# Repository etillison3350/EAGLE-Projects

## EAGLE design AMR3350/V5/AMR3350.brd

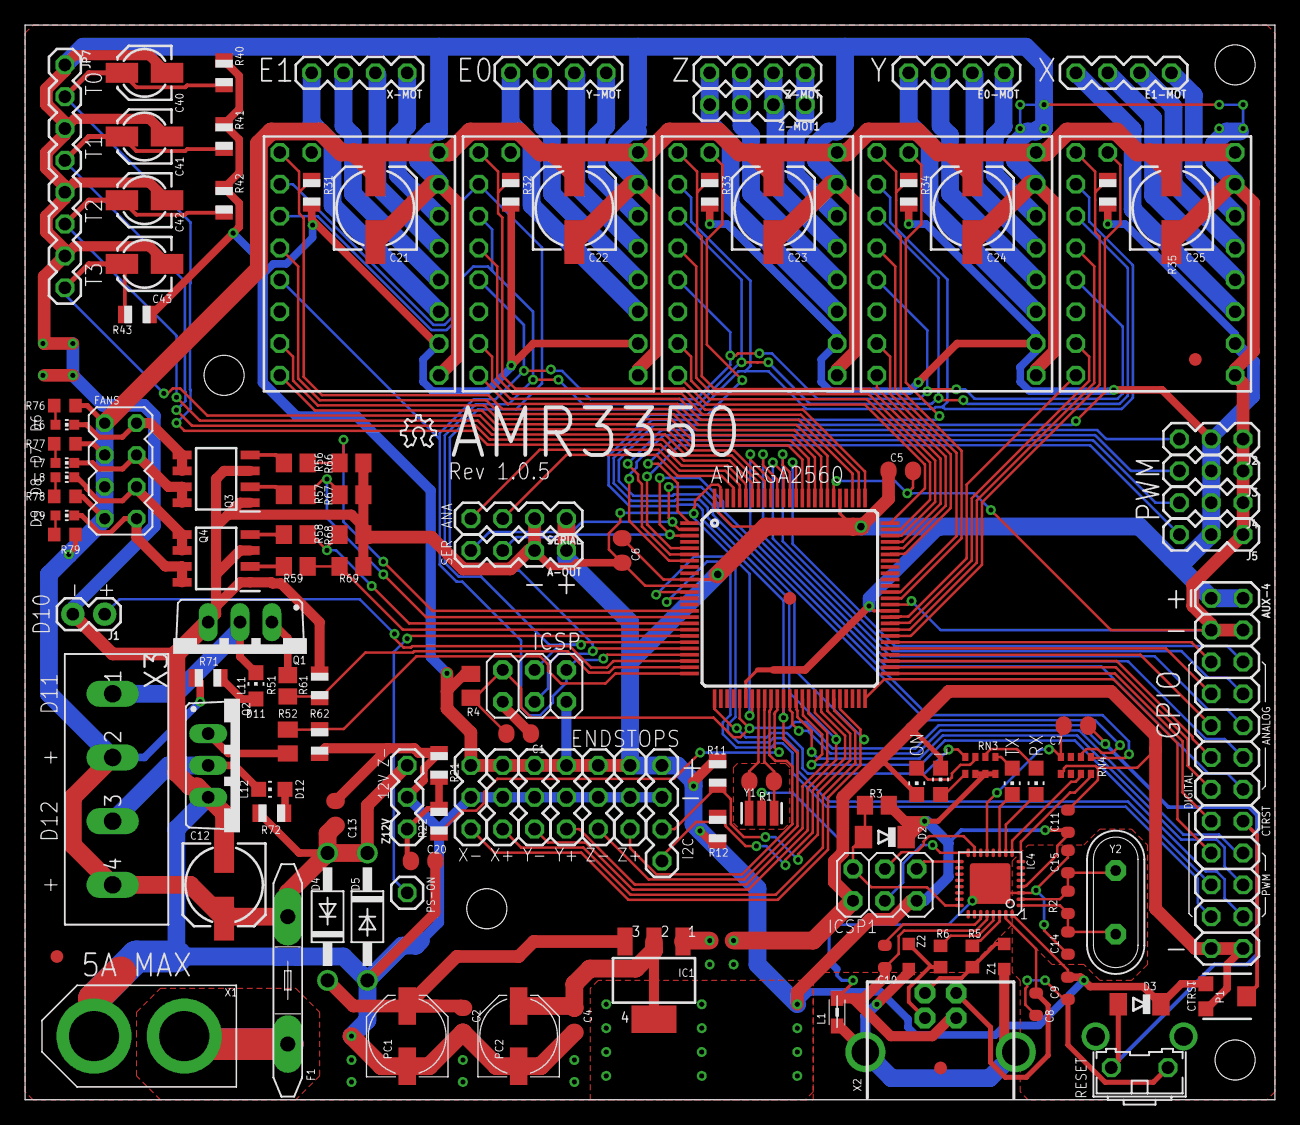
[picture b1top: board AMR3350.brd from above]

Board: 2 copper layers, 99.7 x 85.7 mm, 135 parts (1 on the bottom side), 141 nets.

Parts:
A-OUT: 1X04_SMALL
ATMEGA2560: ATMEGA2560-16AU; TQFP100
AUX-4: CONN_12X2SMALL; 2X12_SMALL
C1: 22p; C0805RND
C2, C4, C5, C6, C7, C13, C20: 100n; C0805RND
C8, C9, C11: 100n; C0603-ROUND
C10: 1u; C0603-ROUND
C12, C21, C22, C23, C24, C25: 100uF; 153CLV-0605
C14, C15: 22p; C0603-ROUND
C40, C41, C42, C43: 10uF; 153CLV-0405
D2, D3: CD1206-S01575; MINIMELF
D4, D5: 1N4004; DO41-10
E0-MOT, E1-MOT: 1X04_SMALL
F1: MFR500
FANS: M04X2; 2X4
FD1, FD2, FD3, FD4: FIDUCIALMOUNT; FIDUCIA-MOUNT
GND: 0; R0201
I2C: 1X04_SMALL
IC1: NCP1117ST50T3G; SOT223
IC4: ATMEGA16U2-MU; MLF32
ICSP, ICSP1: 3x2M; 2X03
J1: 1X02
J2, J3, J4, J5: 455-1750-1-ND; 1X03_SMALL
JP7: 1X08_SMALL
L: RED; CHIP-LED0805
L1: BLM21; 0805
L6, L7, L8, L9: CHIP-LED0603
L11, L12: CHIP-LED0805
LOGO2: OSHW_LOGO_6MILX0100-NT; OSHW_6X100_NOTEXT
ON: GREEN; CHIP-LED0805
P1: TC33X-2-103E; TC33X-2_1
PC1, PC2: 47u; PANASONIC_D
PS-ON: 1X01_SMALL
Q1, Q2: STP55NF06L; TO220BV
Q3, Q4: SI4946CDY-T1-GE3; SOIC127P600X175-8N
R1: 1M; R0805RND
R2: 1M; R0603-ROUND
R3, R4, R21, R31, R32, R33, R34, R35: 10k; R0805
R5, R6: 22R; R0603
R11, R12: 3.3K; R0805
R22: 15k; R0805
R40, R41, R42, R43: 4.7K; R0805
R51: 10r; R0805
R52: 10r; M0805
R56, R57, R58, R59: 10R; R0805
R61, R62, R66, R67, R68, R69: 100k; R0805
R71, R72: 1.8K; R0805
R76, R77, R78, R79: R0603
RESET: B3F-31XX
RN3, RN4: 1k; CAY16
RX: YELLOW; CHIP-LED0805
SERIAL: 1X04_SMALL
TX: YELLOW; CHIP-LED0805
U$1, U$2, U$3, U$4, U$5: TMC2130BREAKOUT
X1: XT60
X2: USB-B_TH; PN61729-NOSILK
X3: 4-PIN
X+: 455-1750-1-ND; 1X03_SMALL
X-: 455-1750-1-ND; 1X03_SMALL
X-MOT: 1X04_SMALL
Y1: CSTCE16M0V53-R0 16MHZ; RESONATOR
Y2: 16MHz; QS
Y+: 455-1750-1-ND; 1X03_SMALL
Y-: 455-1750-1-ND; 1X03_SMALL
Y-MOT: 1X04_SMALL
Z1, Z2: CG0603MLC-05E; CT/CN0603
Z12V: 455-1750-1-ND; 1X03_SMALL
Z+: 455-1750-1-ND; 1X03_SMALL
Z-: 455-1750-1-ND; 1X03_SMALL
Z-MOT, Z-MOT1: 1X04_SMALL

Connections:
12V-IN: F1.2, X1.P$1
+5V: A-OUT.1, ATMEGA2560.10, ATMEGA2560.31, ATMEGA2560.61, ATMEGA2560.80, ATMEGA2560.100, AUX-4.1, AUX-4.2, C4.1, C5.1, C6.1, C9.1, C11.1, D2.C, D3.C, I2C.1, IC1.2, IC1.4, IC4.4, IC4.32, ICSP.2, ICSP1.2, J2.2, J3.2, J4.2, J5.2, P1.1, PC2.+, R3.2, R4.2, R11.2, R12.2, R31.1, R32.1, R33.1, R34.1, R35.1, R40.2, R41.2, R42.2, R43.2, RN3.2, RN3.3, RN3.4, SERIAL.1, U$1.VIO, U$2.VIO, U$3.VIO, U$4.VIO, U$5.VIO, X+.3, X-.3, Y+.3, Y-.3, Z+.3, Z-.3
+12V: C12.+, C13.1, C21.+, C22.+, C23.+, C24.+, C25.+, D4.A, D5.C, F1.1, FANS.1, FANS.3, FANS.5, FANS.7, R71.1, R72.1, R76.2, R77.2, R78.2, R79.2, U$1.VM, U$2.VM, U$3.VM, U$4.VM, U$5.VM, X3.2, X3.4, Z12V.3
A0: ATMEGA2560.97, SERIAL.3
A1: ATMEGA2560.96, SERIAL.4
A2: ATMEGA2560.95, C40.+, JP7.2, R40.1
A3: ATMEGA2560.94, C41.+, JP7.4, R41.1
A4: ATMEGA2560.93, C42.+, JP7.6, R42.1
A5: ATMEGA2560.92, C43.+, JP7.8, R43.1
A6: ATMEGA2560.91, AUX-4.14
A7: ATMEGA2560.90, AUX-4.12
A8: ATMEGA2560.89, AUX-4.10
A9: ATMEGA2560.88, AUX-4.8
A10: ATMEGA2560.87, AUX-4.6
A11: ATMEGA2560.86, U$1.DIR
A12: ATMEGA2560.85, U$1.STEP
A13: ATMEGA2560.84, U$1.CFG-3
A14: ATMEGA2560.83, R31.2, U$1.CFG-6
A15: ATMEGA2560.82, U$2.DIR
CTRST: AUX-4.16, P1.2
D0: A-OUT.4, ATMEGA2560.2, RN4.2
D1: A-OUT.3, ATMEGA2560.3, RN4.1
D2: ATMEGA2560.6, J2.3
D3: ATMEGA2560.7, J3.3
D4: ATMEGA2560.1, J4.3
D5: ATMEGA2560.5, J5.3
D6: ATMEGA2560.15, R56.1, R66.1
D7: ATMEGA2560.16, R57.1, R67.1
D8: ATMEGA2560.17, R58.1, R68.1
D9: ATMEGA2560.18, R59.1, R69.1
D10: ATMEGA2560.23, J1.1
D11: ATMEGA2560.24, R51.1, R61.1
D12: ATMEGA2560.25, R52.1, R62.1
D13(LED): ATMEGA2560.26, RN3.8
D14: ATMEGA2560.64, U$5.CFG-3
D15: ATMEGA2560.63, R34.2, U$5.CFG-6
D16: ATMEGA2560.13, AUX-4.21
D17: ATMEGA2560.12, AUX-4.19
D18: ATMEGA2560.46, U$4.IREF, X-.1
D19: ATMEGA2560.45, X+.1
D22: ATMEGA2560.78, U$2.STEP
D23: ATMEGA2560.77, U$2.CFG-3
D24: ATMEGA2560.76, R32.2, U$2.CFG-6
D25: ATMEGA2560.75, U$3.DIR
D26: ATMEGA2560.74, U$3.STEP
D27: ATMEGA2560.73, U$3.CFG-3
D28: ATMEGA2560.72, R33.2, U$3.CFG-6
D29: ATMEGA2560.71, U$5.DIR
D30: ATMEGA2560.60, U$4.DIR
D31: ATMEGA2560.59, U$4.STEP
D32: ATMEGA2560.58, U$4.CFG-3
D33: ATMEGA2560.57, R35.2, U$4.CFG-6
D34: ATMEGA2560.56, AUX-4.5
D35: ATMEGA2560.55, AUX-4.7
D36: ATMEGA2560.54, AUX-4.9
D37: ATMEGA2560.53, AUX-4.11
D38: ATMEGA2560.50, AUX-4.17
D39: ATMEGA2560.70, U$5.STEP
D40: ATMEGA2560.52, AUX-4.13
D41: ATMEGA2560.51, AUX-4.15
D42: ATMEGA2560.42, U$5.IREF, Y-.1
D43: ATMEGA2560.41, Y+.1
D44: ATMEGA2560.40, AUX-4.22
D45: ATMEGA2560.39, AUX-4.20
D46: ATMEGA2560.38, AUX-4.18
D47: ATMEGA2560.37, U$3.IREF, Z-.1
D48: ATMEGA2560.36, R22.1
D49: ATMEGA2560.35, Z+.1
D53: ATMEGA2560.19, PS-ON.1
D+: R6.2, X2.3, Z2.2
D-: R5.2, X2.2, Z1.2
DTR: C7.1, IC4.13, RN4.4
E0-1: E0-MOT.1, U$5.OB2
E0-2: E0-MOT.2, U$5.OB1
E0-3: E0-MOT.3, U$5.OA1
E0-4: E0-MOT.4, U$5.OA2
E1-1: E1-MOT.1, U$4.OB2
E1-2: E1-MOT.2, U$4.OB1
E1-3: E1-MOT.3, U$4.OA1
E1-4: E1-MOT.4, U$4.OA2
GND: A-OUT.2, ATMEGA2560.11, ATMEGA2560.32, ATMEGA2560.62, ATMEGA2560.81, ATMEGA2560.99, AUX-4.3, AUX-4.4, AUX-4.23, AUX-4.24, C1.2, C2.2, C4.2, C5.2, C6.2, C8.2, C9.2, C11.2, C12.-, C13.2, C14.2, C15.2, C20.2, C21.-, C22.-, C23.-, C24.-, C25.-, C40.-, C41.-, C42.-, C43.-, D5.A, GND.2, I2C.2, IC1.1, IC4.3, IC4.33, ICSP.6, ICSP1.6, J1.2, J2.1, J3.1, J4.1, J5.1, JP7.1, JP7.3, JP7.5, JP7.7, L.C, ON.C, P1.3, PC1.-, PC2.-, Q1.S, Q2.S, Q3.1, Q3.3, Q4.1, Q4.3, R21.1, R61.2, R62.2, R66.2, R67.2, R68.2, R69.2, RESET.2, RN4.5, SERIAL.2, U$1.GND, U$1.GND@0, U$2.GND, U$2.GND@0, U$3.GND, U$3.GND@0, U$4.GND, U$4.GND@0, U$5.GND, U$5.GND@0, X1.P$2, X+.2, X-.2, Y1.2, Y+.2, Y-.2, Z12V.2, Z+.2, Z-.2
L: L.A, RN3.1
M8RXD: IC4.9, RN4.7
M8TXD: IC4.8, RN4.8
MISO: ATMEGA2560.22, ICSP.1, U$1.CFG-0, U$2.CFG-0, U$3.CFG-0, U$4.CFG-0, U$5.CFG-0
MISO2: IC4.17, ICSP1.1
MOSI: ATMEGA2560.21, ICSP.4, U$1.CFG-1, U$2.CFG-1, U$3.CFG-1, U$4.CFG-1, U$5.CFG-1
MOSI2: IC4.16, ICSP1.4
unnamed: L9.A, R79.1
unnamed: L8.A, R78.1
unnamed: C20.1, R21.2, R22.2, Z12V.1
unnamed: L6.A, R76.1
unnamed: L7.A, R77.1
unnamed: L12.A, R72.2
unnamed: L11.A, R71.2
ON: ON.A, RN3.7
Q1-D: L11.C, Q1.D, X3.1
Q1-G: Q1.G, R51.2
Q2-D: L12.C, Q2.D, X3.3
Q2-G: Q2.G, R52.2
Q6-D: FANS.2, L6.C, Q3.5, Q3.6
Q6-G: Q3.4, R56.2
Q7-D: FANS.4, L7.C, Q3.7, Q3.8
Q7-G: Q3.2, R57.2
Q8-D: FANS.6, L8.C, Q4.5, Q4.6
Q8-G: Q4.4, R58.2
Q9-D: FANS.8, L9.C, Q4.7, Q4.8
Q9-G: Q4.2, R59.2
RD+: IC4.29, R6.1
RD-: IC4.30, R5.1
RESET: ATMEGA2560.30, C1.1, C7.2, D3.A, ICSP.5, R4.1, RESET.1
RESET2: D2.A, IC4.24, ICSP1.5, R3.1
RX: RN3.6, RX.A
RXL: IC4.10, RX.C
SCK: ATMEGA2560.20, ICSP.3, U$1.CFG-2, U$2.CFG-2, U$3.CFG-2, U$4.CFG-2, U$5.CFG-2
SCK2: IC4.15, ICSP1.3
SCL: ATMEGA2560.43, I2C.4, R12.1
SDA: ATMEGA2560.44, I2C.3, R11.1
TX: RN3.5, TX.A
TXL: IC4.11, TX.C
UGND: C10.2, GND.1, IC4.28, L1.1, X2.4
USBVCC: C8.1, IC4.31, X2.1
USHIELD: L1.2, X2.P$1, X2.P$2, Z1.1, Z2.1
VIN: C2.1, D4.C, IC1.3, PC1.+
VUCAP: C10.1, IC4.27
X-1: U$1.OB2, X-MOT.1
X-2: U$1.OB1, X-MOT.2
X-3: U$1.OA1, X-MOT.3
X-4: U$1.OA2, X-MOT.4
XT1: C14.1, IC4.1, R2.1, Y2.2
XT2: C15.1, IC4.2, R2.2, Y2.1
XTAL1: ATMEGA2560.34, R1.1, Y1.3
XTAL2: ATMEGA2560.33, R1.2, Y1.1
Y-1: U$2.OB2, Y-MOT.1
Y-2: U$2.OB1, Y-MOT.2
Y-3: U$2.OA1, Y-MOT.3
Y-4: U$2.OA2, Y-MOT.4
Z-1: U$3.OB2, Z-MOT.1, Z-MOT1.1
Z-2: U$3.OB1, Z-MOT.2, Z-MOT1.2
Z-3: U$3.OA1, Z-MOT.3, Z-MOT1.3
Z-4: U$3.OA2, Z-MOT.4, Z-MOT1.4

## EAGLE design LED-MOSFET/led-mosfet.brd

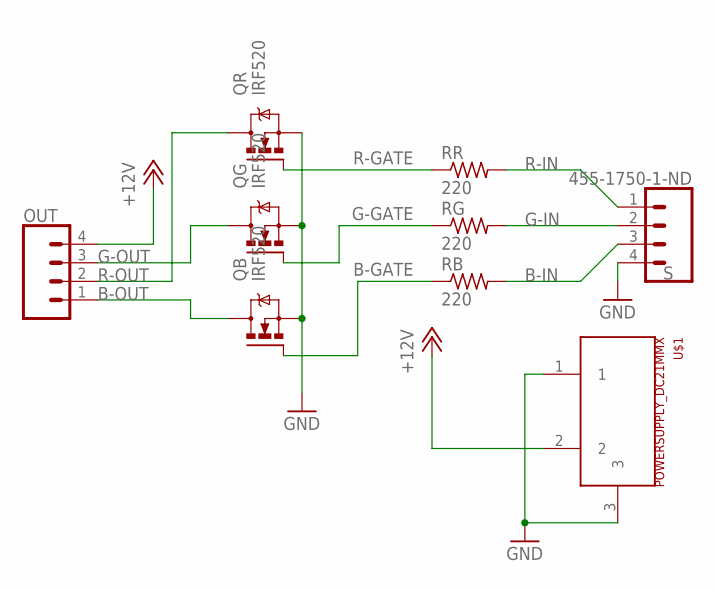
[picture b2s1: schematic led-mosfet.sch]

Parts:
OUT: CONN_04; 1X04
QB: IRF520; TO220BV
QG: IRF520; TO220BV
QR: IRF520; TO220BV
RB: 220; R0805
RG: 220; R0805
RR: 220; R0805
S: 455-1750-1-ND; 1X04
U$1: POWERSUPPLY_DC21MMX; POWERSUPPLY_DC-21MM

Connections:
+12V: OUT.4, U$1.2
B-GATE: QB.G, RB.1
B-IN: RB.2, S.3
B-OUT: OUT.1, QB.D
G-GATE: QG.G, RG.1
G-IN: RG.2, S.2
G-OUT: OUT.3, QG.D
GND: QB.S, QG.S, QR.S, S.4, U$1.1, U$1.3
R-GATE: QR.G, RR.1
R-IN: RR.2, S.1
R-OUT: OUT.2, QR.D

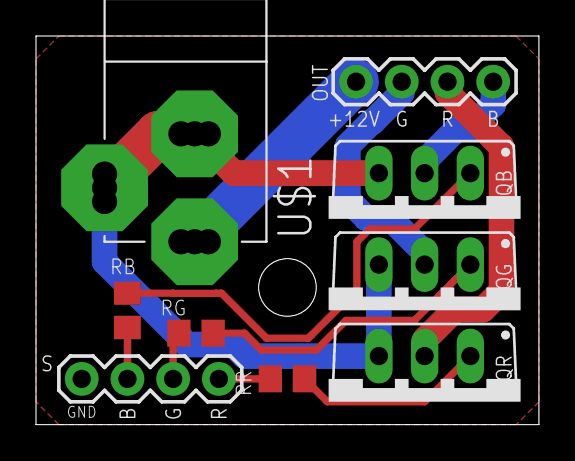
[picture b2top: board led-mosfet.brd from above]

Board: 2 copper layers, 27.9 x 21.6 mm, 9 parts (0 on the bottom side), 11 nets.

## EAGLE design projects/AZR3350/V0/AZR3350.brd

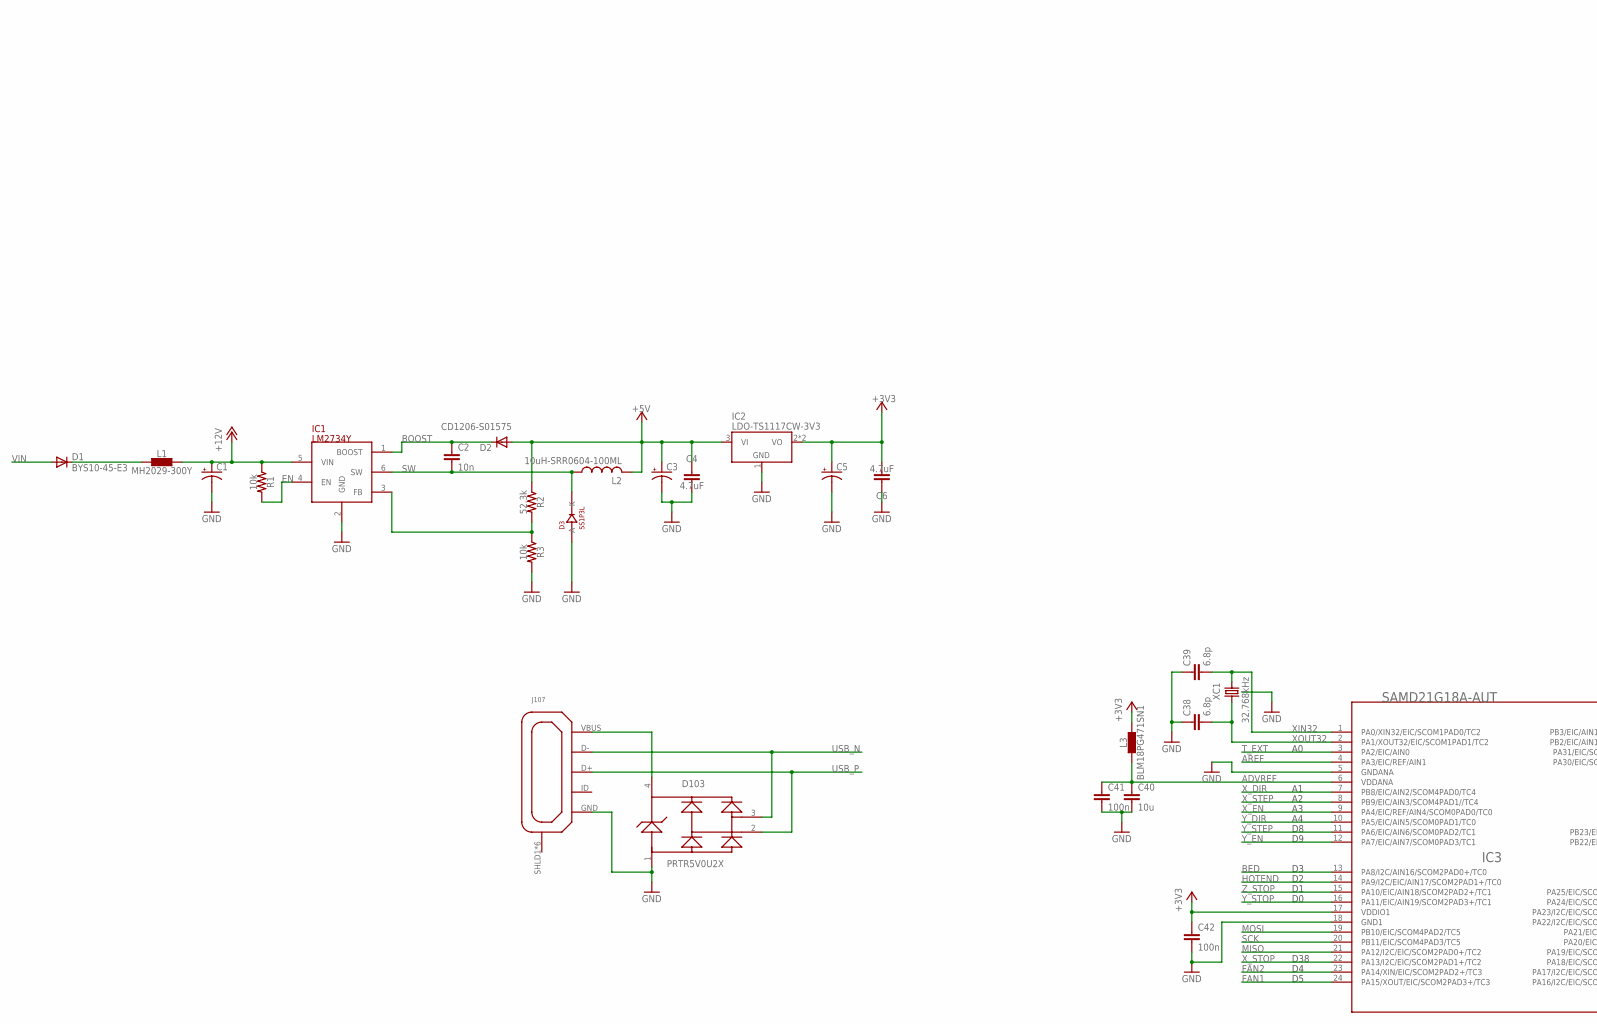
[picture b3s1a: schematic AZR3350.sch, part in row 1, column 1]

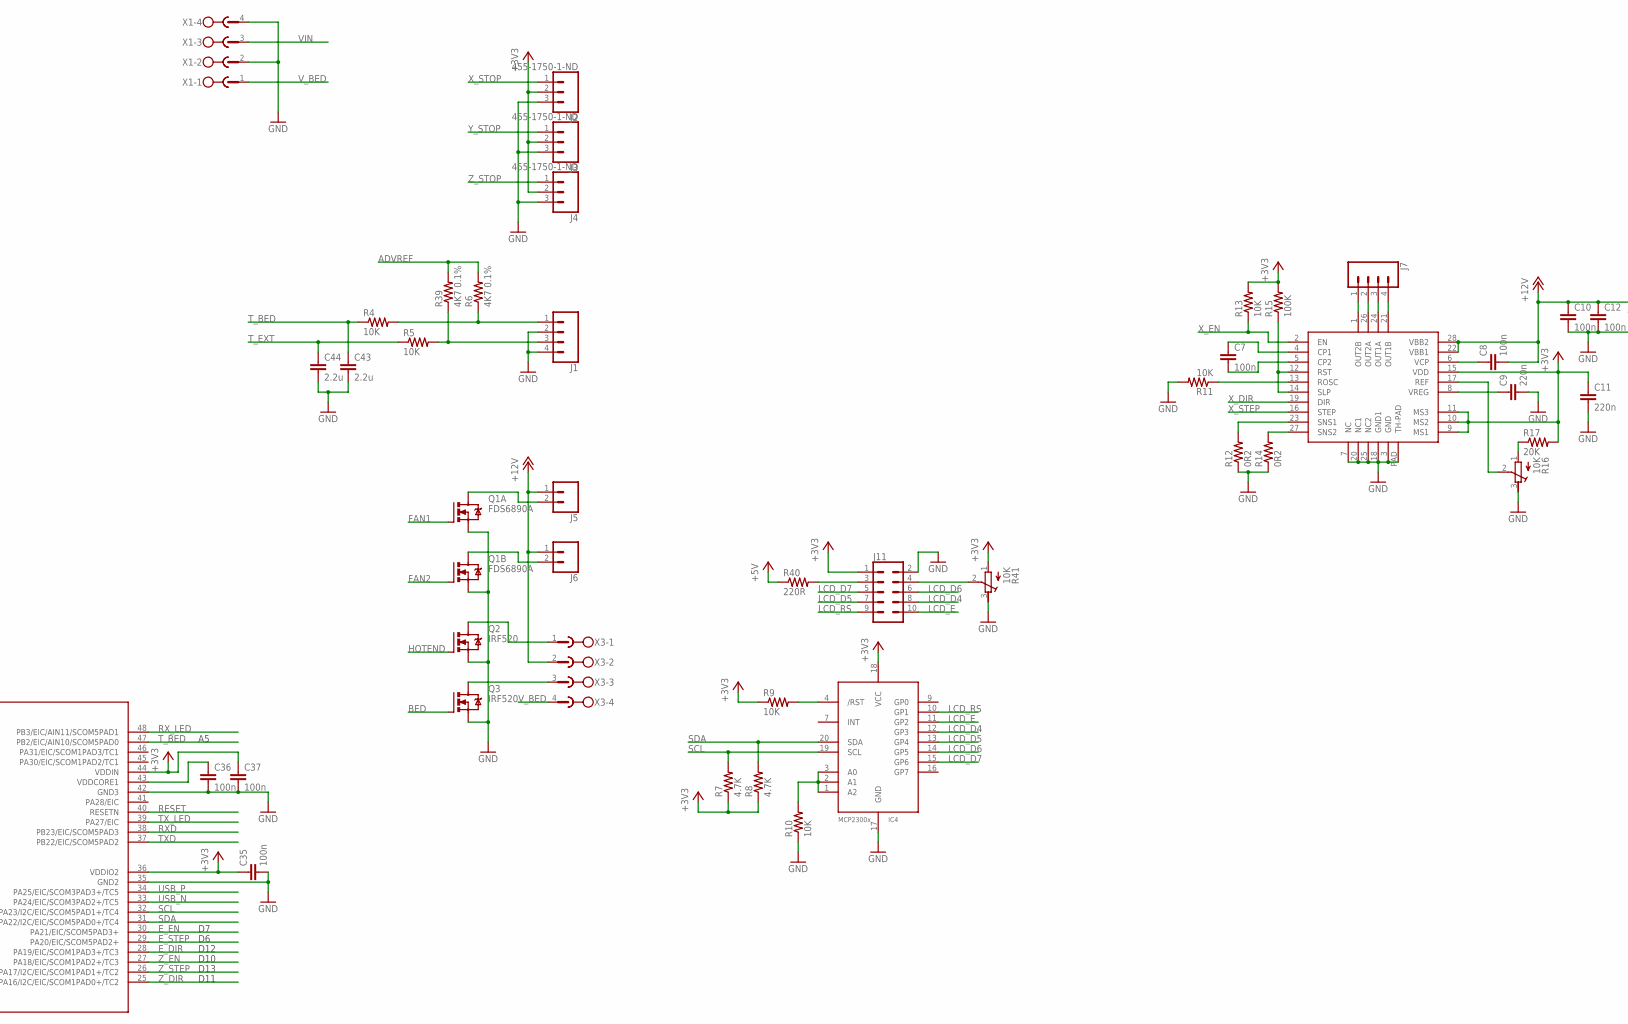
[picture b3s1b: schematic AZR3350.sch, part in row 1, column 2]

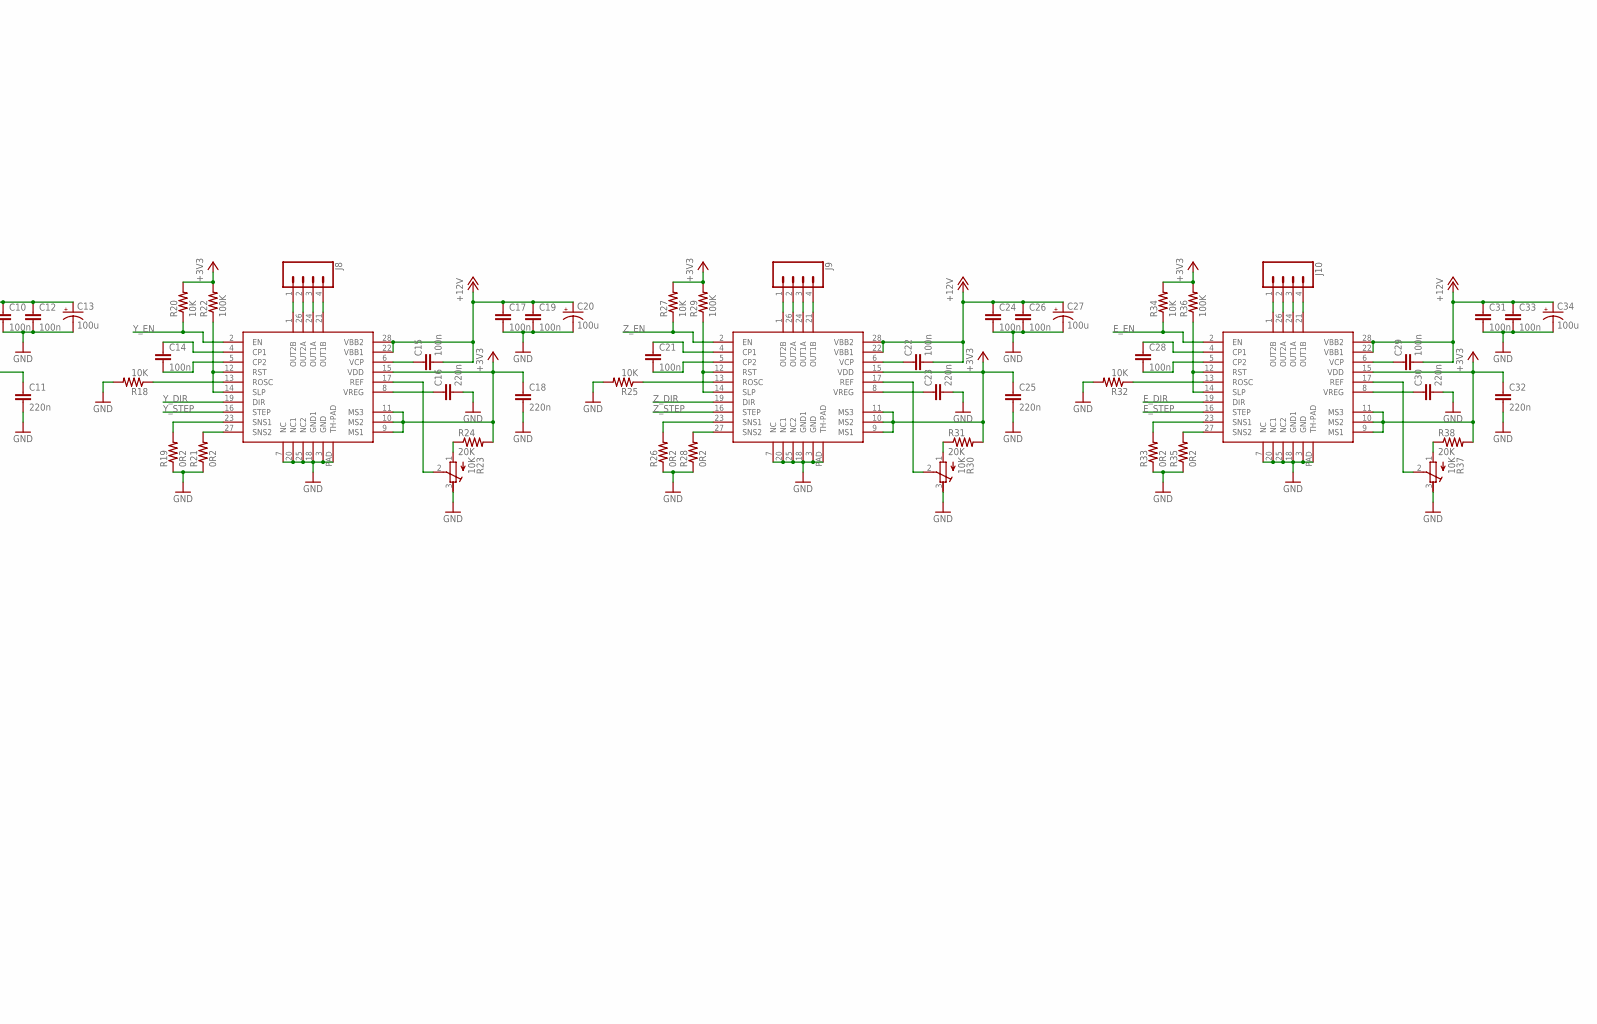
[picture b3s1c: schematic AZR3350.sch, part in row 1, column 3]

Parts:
C1, C5: 10uF; PANASONIC_D
C2: 10n; C0402
C3: 47u; PANASONIC_D
C4, C6: 4.7uF; C0402
C7, C8, C10, C12, C14, C15, C17, C19, C21, C22, C24, C26, C28, C29, C31, C33, C35, C36, C37, C41, C42: 100n; C0402
C9, C11, C16, C18, C23, C25, C30, C32: 220n; C0402
C13, C20, C27, C34: 100u; PANASONIC_D
C38, C39: 6.8p; C0402
C40: 10u; C0603
C43, C44: 2.2u; C0402
D1: BYS10-45-E3; MINIMELF
D2: CD1206-S01575; MINIMELF
D3: SS1P3L; DO220AAL
D103: PRTR5V0U2XB; SOT143B
IC1: LM2734Y; SOT23-6
IC2: LDO-TS1117CW-3V3; SOT223
IC3: SAMD21G18A-AUT; TQFP48
IC4: MCP23008; QFN20
IC5, IC6, IC7, IC8: A4988; QFN28-TP
J1, J7, J8, J9, J10: CONN_04; 1X04
J2, J3, J4: 455-1750-1-ND; 1X03
J5, J6: CONN_02; 1X02
J11: CONN_05X2PTH; 2X5
J107: ZX62-AB-5PA; USB-MICRO-10103594
L1: MH2029-300Y; C0805
L2: 10uH-SRR0604-100ML; SRR0604
L3: BLM18PG471SN1; C0603
Q1: FDS6890A; M08A
Q2, Q3: IRF520; TO220BV
R1, R3: 10k; R0402
R2: 52.3k; R0402
R4, R5, R9, R10, R11, R13, R18, R20, R25, R27, R32, R34: 10K; R0402
R6, R39: 4K7 0.1%; R0402
R7, R8: 4.7K; R0402
R12, R14, R19, R21, R26, R28, R33, R35: 0R2; R0805
R15, R22, R29, R36: 100K; R0402
R16, R23, R30, R37, R41: 10K; RTRIM3103
R17, R24, R31, R38: 20K; R0402
R40: 220R; R0402
X1: MSTBA4
X3: MSTBV4
XC1: 32.768kHz; CRYSTAL_TC26SMD

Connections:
+3V3: C5.+, C6.2, C11.1, C18.1, C25.1, C32.1, C35.1, C37.1, C42.1, IC2.2 (VO), IC2.4 (VO), IC3.17 (VDDIO1), IC3.36 (VDDIO2), IC3.44 (VDDIN), IC4.18 (VCC), IC5.9 (MS1), IC5.10 (MS2), IC5.11 (MS3), IC5.15 (VDD), IC6.9 (MS1), IC6.10 (MS2), IC6.11 (MS3), IC6.15 (VDD), IC7.9 (MS1), IC7.10 (MS2), IC7.11 (MS3), IC7.15 (VDD), IC8.9 (MS1), IC8.10 (MS2), IC8.11 (MS3), IC8.15 (VDD), J2.2, J3.2, J4.2, J11.1, L3.2, R7.1, R8.1, R9.1, R13.2, R15.2, R17.2, R20.2, R22.2, R24.2, R27.2, R29.2, R31.2, R34.2, R36.2, R38.2, R41.1 (A)
+5V: C3.+, C4.1, D2.A, IC2.3 (VI), L2.P$2 (2), R2.1, R40.1
+12V: C1.+, C8.2, C10.1, C12.1, C13.+, C15.2, C17.1, C19.1, C20.+, C22.2, C24.1, C26.1, C27.+, C29.2, C31.1, C33.1, C34.+, IC1.5 (VIN), IC5.22 (VBB1), IC5.28 (VBB2), IC6.22 (VBB1), IC6.28 (VBB2), IC7.22 (VBB1), IC7.28 (VBB2), IC8.22 (VBB1), IC8.28 (VBB2), J5.1, J6.1, L1.2, R1.1, X3.2
ADVREF: C40.1, C41.1, IC3.6 (VDDANA), L3.1, R6.2, R39.2
AREF: IC3.4 (PA3/EIC/REF/AIN1)
BED: IC3.13 (PA8/I2C/AIN16/SCOM2PAD0+/TC0), Q3.G
BOOST: C2.1, D2.C, IC1.1 (BOOST)
CP1E: C28.1, IC8.4 (CP1)
CP1X: C7.1, IC5.4 (CP1)
CP1Y: C14.1, IC6.4 (CP1)
CP1Z: C21.1, IC7.4 (CP1)
CP2E: C28.2, IC8.5 (CP2)
CP2X: C7.2, IC5.5 (CP2)
CP2Y: C14.2, IC6.5 (CP2)
CP2Z: C21.2, IC7.5 (CP2)
EN: IC1.4 (EN), R1.2
E_DIR: IC3.28 (PA19/EIC/SCOM1PAD3+/TC3), IC8.19 (DIR)
E_EN: IC3.30 (PA21/EIC/SCOM5PAD3+), IC8.2 (EN), R34.1
E_STEP: IC3.29 (PA20/EIC/SCOM5PAD2+), IC8.16 (STEP)
FAN1: IC3.24 (PA15/XOUT/EIC/SCOM2PAD3+/TC3), Q1.2 (G)
FAN2: IC3.23 (PA14/XIN/EIC/SCOM2PAD2+/TC3), Q1.4 (G)
FB: IC1.3 (FB), R2.2, R3.1
GND: C1.-, C3.-, C4.2, C5.-, C6.1, C9.2, C10.2, C11.2, C12.2, C13.-, C16.2, C17.2, C18.2, C19.2, C20.-, C23.2, C24.2, C25.2, C26.2, C27.-, C30.2, C31.2, C32.2, C33.2, C34.-, C35.2, C36.2, C37.2, C38.1, C39.1, C40.2, C41.2, C42.2, C43.2, C44.2, D3.P$2 (A), D103.1, IC1.2 (GND), IC2.1 (GND), IC3.5 (GNDANA), IC3.18 (GND1), IC3.35 (GND2), IC3.42 (GND3), IC4.17 (GND), IC5.3 (GND), IC5.7 (NC), IC5.18 (GND1), IC5.20 (NC1), IC5.25 (NC2), IC5.PAD (TH-PAD), IC6.3 (GND), IC6.7 (NC), IC6.18 (GND1), IC6.20 (NC1), IC6.25 (NC2), IC6.PAD (TH-PAD), IC7.3 (GND), IC7.7 (NC), IC7.18 (GND1), IC7.20 (NC1), IC7.25 (NC2), IC7.PAD (TH-PAD), IC8.3 (GND), IC8.7 (NC), IC8.18 (GND1), IC8.20 (NC1), IC8.25 (NC2), IC8.PAD (TH-PAD), J1.2, J1.4, J2.3, J3.3, J4.3, J11.2, J107.GND, Q1.1 (S), Q1.3 (S), Q2.S, Q3.S, R3.2, R10.1, R11.2, R12.1, R14.1, R16.3 (E), R18.2, R19.1, R21.1, R23.3 (E), R25.2, R26.1, R28.1, R30.3 (E), R32.2, R33.1, R35.1, R37.3 (E), R41.3 (E), X1.2, X1.4, XC1.P$1 (GND)
HOTEND: IC3.14 (PA9/I2C/EIC/AIN17/SCOM2PAD1+/TC0), Q2.G
LCD_D4: IC4.12 (GP3), J11.8
LCD_D5: IC4.13 (GP4), J11.7
LCD_D6: IC4.14 (GP5), J11.6
LCD_D7: IC4.15 (GP6), J11.5
LCD_E: IC4.11 (GP2), J11.10
LCD_RS: IC4.10 (GP1), J11.9
MISO: IC3.21 (PA12/I2C/EIC/SCOM2PAD0+/TC2)
MOSI: IC3.19 (PB10/EIC/SCOM4PAD2/TC5)
unnamed: D1.C, L1.1
unnamed: J1.1, R4.2, R6.1
unnamed: J1.3, R5.2, R39.1
unnamed: IC6.12 (RST), IC6.14 (SLP), R22.1
unnamed: J11.3, R40.2
unnamed: IC5.1 (OUT2B), J7.1
unnamed: IC5.26 (OUT2A), J7.2
unnamed: IC5.24 (OUT1A), J7.3
unnamed: IC5.21 (OUT1B), J7.4
unnamed: J11.4, R41.2 (S)
unnamed: D103.4, J107.VBUS (VUSB)
unnamed: IC6.1 (OUT2B), J8.1
unnamed: IC6.26 (OUT2A), J8.2
unnamed: IC6.24 (OUT1A), J8.3
unnamed: IC6.21 (OUT1B), J8.4
unnamed: R23.1 (A), R24.1
unnamed: J6.2, Q1.5 (D), Q1.6 (D)
unnamed: J5.2, Q1.7 (D), Q1.8 (D)
unnamed: Q2.D, X3.1
unnamed: Q3.D, X3.3
unnamed: IC4.4 (/RST), R9.2
unnamed: IC4.1 (A2), IC4.2 (A1), IC4.3 (A0), R10.2
unnamed: IC5.12 (RST), IC5.14 (SLP), R15.1
unnamed: R16.1 (A), R17.1
unnamed: IC7.12 (RST), IC7.14 (SLP), R29.1
unnamed: IC7.1 (OUT2B), J9.1
unnamed: IC7.26 (OUT2A), J9.2
unnamed: IC7.24 (OUT1A), J9.3
unnamed: IC7.21 (OUT1B), J9.4
unnamed: R30.1 (A), R31.1
unnamed: IC8.12 (RST), IC8.14 (SLP), R36.1
unnamed: IC8.1 (OUT2B), J10.1
unnamed: IC8.26 (OUT2A), J10.2
unnamed: IC8.24 (OUT1A), J10.3
unnamed: IC8.21 (OUT1B), J10.4
unnamed: R37.1 (A), R38.1
REFE: IC8.17 (REF), R37.2 (S)
REFX: IC5.17 (REF), R16.2 (S)
REFY: IC6.17 (REF), R23.2 (S)
REFZ: IC7.17 (REF), R30.2 (S)
RESET: IC3.40 (RESETN)
ROSCE: IC8.13 (ROSC), R32.1
ROSCX: IC5.13 (ROSC), R11.1
ROSCY: IC6.13 (ROSC), R18.1
ROSCZ: IC7.13 (ROSC), R25.1
RXD: IC3.38 (PB23/EIC/SCOM5PAD3)
RX_LED: IC3.48 (PB3/EIC/AIN11/SCOM5PAD1)
SCK: IC3.20 (PB11/EIC/SCOM4PAD3/TC5)
SCL: IC3.32 (PA23/I2C/EIC/SCOM5PAD1+/TC4), IC4.19 (SCL), R7.2
SDA: IC3.31 (PA22/I2C/EIC/SCOM5PAD0+/TC4), IC4.20 (SDA), R8.2
SNS1E: IC8.23 (SNS1), R33.2
SNS1X: IC5.23 (SNS1), R12.2
SNS1Y: IC6.23 (SNS1), R19.2
SNS1Z: IC7.23 (SNS1), R26.2
SNS2E: IC8.27 (SNS2), R35.2
SNS2X: IC5.27 (SNS2), R14.2
SNS2Y: IC6.27 (SNS2), R21.2
SNS2Z: IC7.27 (SNS2), R28.2
SW: C2.2, D3.P$1 (K), IC1.6 (SW), L2.P$1 (1)
TXD: IC3.37 (PB22/EIC/SCOM5PAD2)
TX_LED: IC3.39 (PA27/EIC)
T_BED: C43.1, IC3.47 (PB2/EIC/AIN10/SCOM5PAD0), R4.1
T_EXT: C44.1, IC3.3 (PA2/EIC/AIN0), R5.1
USB_N: D103.3, IC3.33 (PA24/EIC/SCOM3PAD2+/TC5), J107.D-
USB_P: D103.2, IC3.34 (PA25/EIC/SCOM3PAD3+/TC5), J107.D+
VCPE: C29.1, IC8.6 (VCP)
VCPX: C8.1, IC5.6 (VCP)
VCPY: C15.1, IC6.6 (VCP)
VCPZ: C22.1, IC7.6 (VCP)
VDDCORE: C36.1, IC3.43 (VDDCORE1)
VIN: D1.A, X1.3
VREGE: C30.1, IC8.8 (VREG)
VREGX: C9.1, IC5.8 (VREG)
VREGY: C16.1, IC6.8 (VREG)
VREGZ: C23.1, IC7.8 (VREG)
V_BED: X1.1, X3.4
XIN32: C39.2, IC3.1 (PA0/XIN32/EIC/SCOM1PAD0/TC2), XC1.2
XOUT32: C38.2, IC3.2 (PA1/XOUT32/EIC/SCOM1PAD1/TC2), XC1.1
X_DIR: IC3.7 (PB8/EIC/AIN2/SCOM4PAD0/TC4), IC5.19 (DIR)
X_EN: IC3.9 (PA4/EIC/REF/AIN4/SCOM0PAD0/TC0), IC5.2 (EN), R13.1
X_STEP: IC3.8 (PB9/EIC/AIN3/SCOM4PAD1//TC4), IC5.16 (STEP)
X_STOP: IC3.22 (PA13/I2C/EIC/SCOM2PAD1+/TC2), J2.1
Y_DIR: IC3.10 (PA5/EIC/AIN5/SCOM0PAD1/TC0), IC6.19 (DIR)
Y_EN: IC3.12 (PA7/EIC/AIN7/SCOM0PAD3/TC1), IC6.2 (EN), R20.1
Y_STEP: IC3.11 (PA6/EIC/AIN6/SCOM0PAD2/TC1), IC6.16 (STEP)
Y_STOP: IC3.16 (PA11/EIC/AIN19/SCOM2PAD3+/TC1), J3.1
Z_DIR: IC3.25 (PA16/I2C/EIC/SCOM1PAD0+/TC2), IC7.19 (DIR)
Z_EN: IC3.27 (PA18/EIC/SCOM1PAD2+/TC3), IC7.2 (EN), R27.1
Z_STEP: IC3.26 (PA17/I2C/EIC/SCOM1PAD1+/TC2), IC7.16 (STEP)
Z_STOP: IC3.15 (PA10/EIC/AIN18/SCOM2PAD2+/TC1), J4.1

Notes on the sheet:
D38
D12
D10
D13
D11

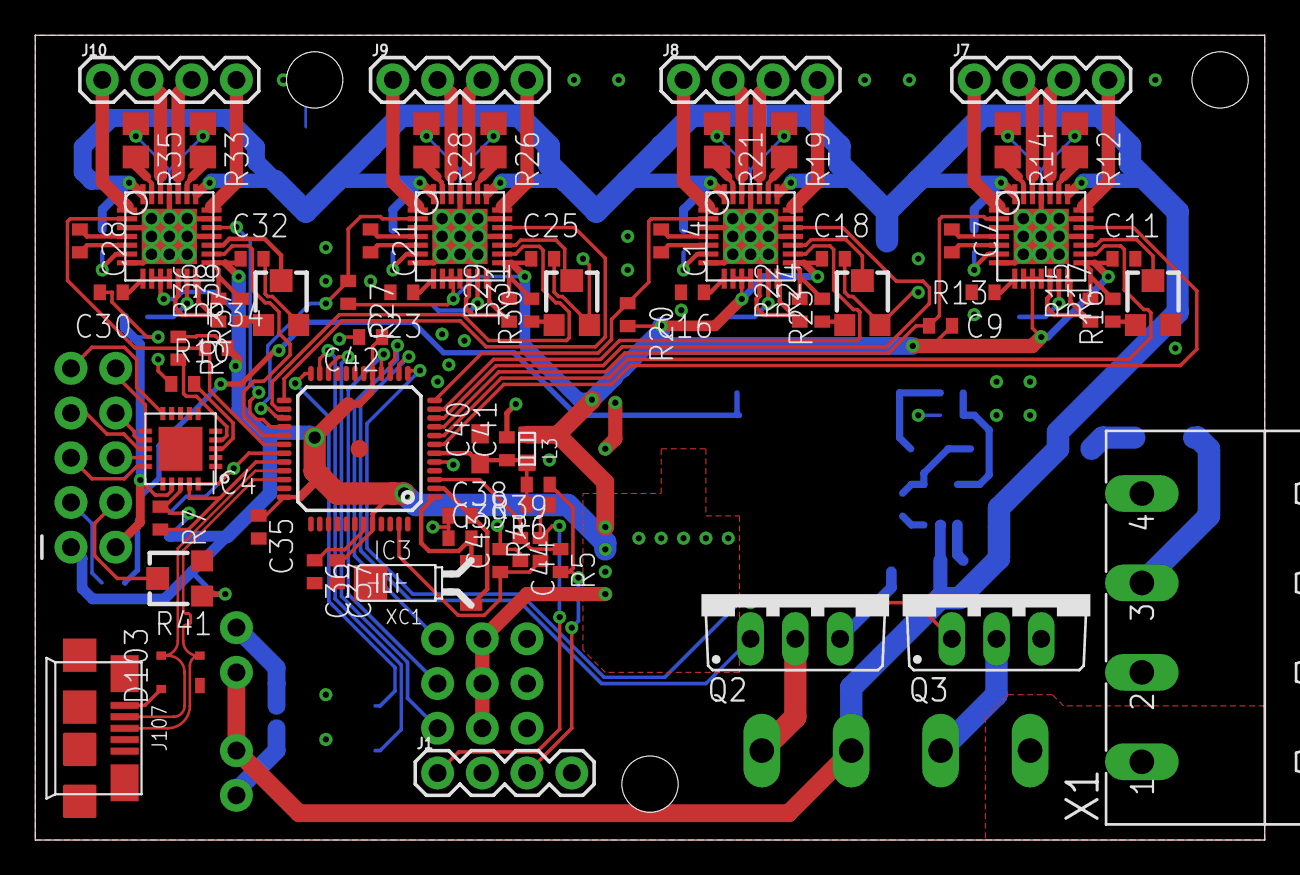
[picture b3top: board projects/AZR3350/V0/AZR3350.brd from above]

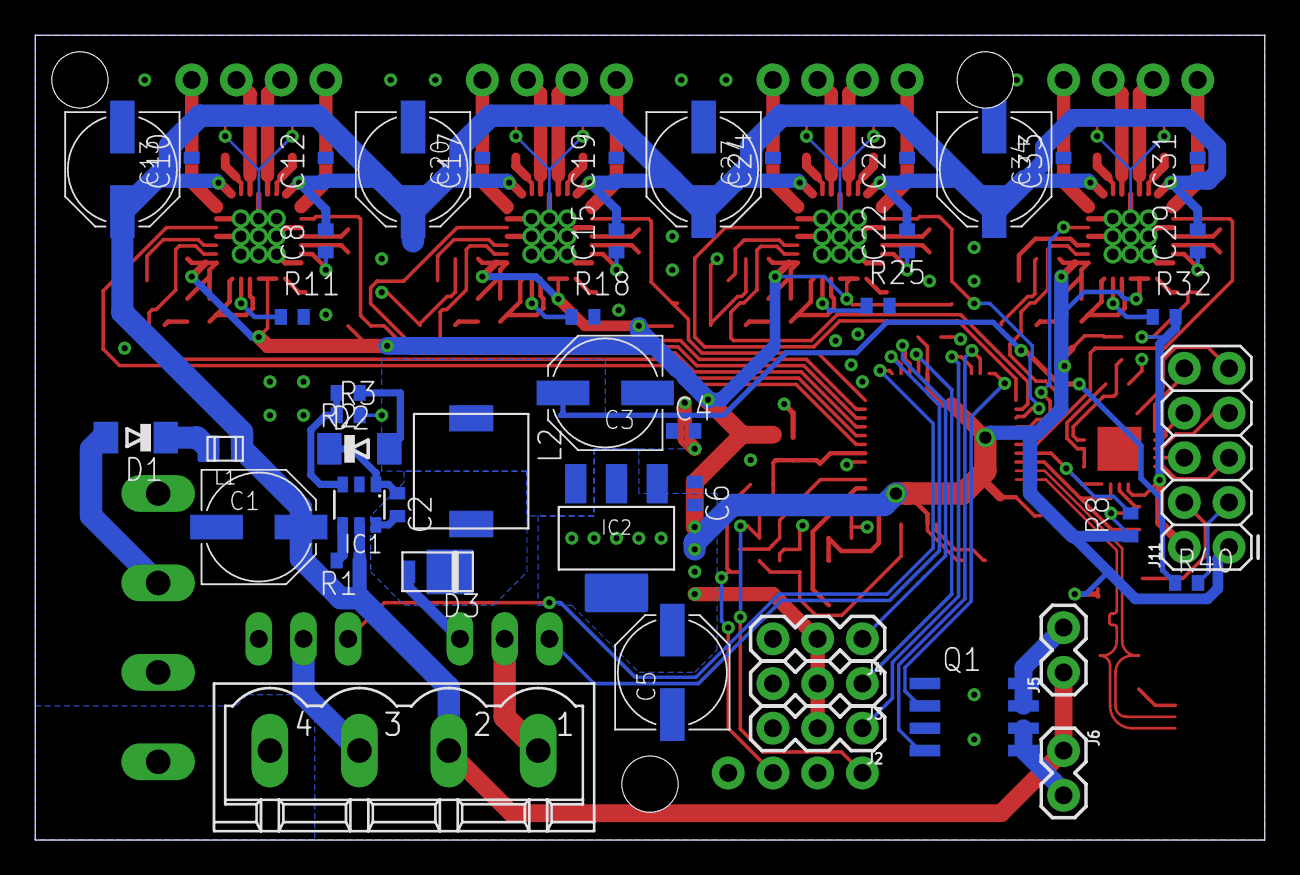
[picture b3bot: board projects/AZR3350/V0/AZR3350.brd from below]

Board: 2 copper layers, 69.8 x 45.7 mm, 118 parts (46 on the bottom side), 113 nets.

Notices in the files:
parts and their libraries:
SparkFun-Connectors: Licensing: Creative Commons ShareAlike 4.0 International - https://creativecommons.org/licenses/by-sa/4.0
